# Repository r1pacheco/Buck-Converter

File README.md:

# Buck-Converter

This buck converter uses a simple switcher, LM2576SX,to hold a steady 3.3V output with the a
certain configuration. My board uses this switch along with schottky diode and an inductor to 
limit a linear range of voltage pass. We have high input voltage (between 12V and 16V) so we
opt for screw terminal input, but use molex outpit pins for the lower voltage output as the
load for this board is a ESP8266 wifi MC that has molex input pins for power.

--------------------------------------PARTS---------------------------------------

Simple Switcher:
https://www.digikey.ca/en/products/detail/texas-instruments/LM2576SX-3-3-NOPB/366792

Diode:
https://www.digikey.ca/en/products/detail/nexperia-usa-inc/BAT760115/1232134

Inductor:
https://www.digikey.ca/en/products/detail/bourns-inc/SRR1806-221M/1129809

Capacitors:
(100uF) https://www.digikey.ca/en/products/detail/nichicon/UWX1C101MCL1GB/589846

(330uF) https://www.digikey.ca/en/products/detail/nichicon/UWT1C331MNL1GS/589921

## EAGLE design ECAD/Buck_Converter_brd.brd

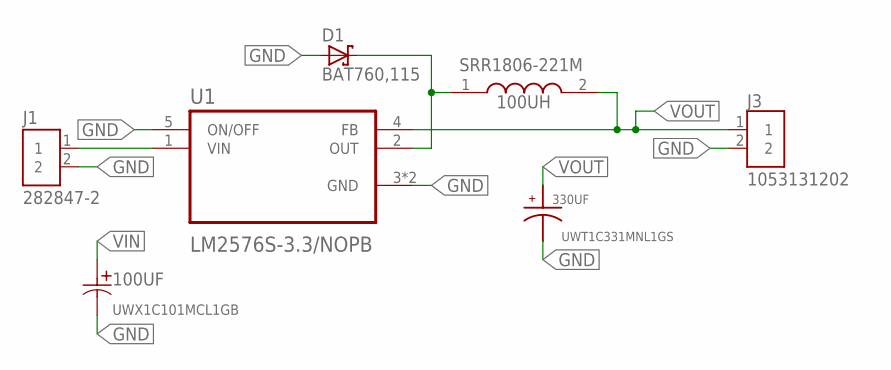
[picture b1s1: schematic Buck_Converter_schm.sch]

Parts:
100UF: UWX1C101MCL1GB; PCAP_6.3X5.4-ELECT_NCA
100UH: SRR1806-221M; SRR1806221M
330UF: UWT1C331MNL1GS; CAPAE830X1080N
D1: BAT760,115; SOD323(F)
J1: 282847-2; TE_282847-2
J3: 1053131202; MOLEX_1053131202
U1: LM2576S-3.3/NOPB; VREG_TPS79625KTTR

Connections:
GND: 100UF.2, 330UF.2, D1.2 (A), J1.2, J3.2, U1.3 (GND), U1.5 (ON/OFF), U1.6 (GND)
unnamed: 100UH.1, D1.1 (K), U1.2 (OUT)
VIN: 100UF.1, J1.1, U1.1 (VIN)
VOUT: 100UH.2, 330UF.1, J3.1, U1.4 (FB)

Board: 2 copper layers, 7 parts (1 on the bottom side), 4 nets, no tracks yet.

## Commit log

2021-10-03 Upload all files
